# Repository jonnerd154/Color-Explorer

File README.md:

# Color-Explorer
A simple PCB to allow students to explore colors and mixing colors of light.

The board provides three slider potentiometers which each control the brightness of one color of light. There are four RGB LEDs. The first three show the individual color component as configured by the position of the sliders - one red, one blue, and one green. The fourth LED shows the mixed/combined colors. A jumper can be removed to disable the "mixed" LED, allowing students to set their sliders and make a hypothesis about what color will result from the mix. After recording their hypothesis, the jumper can be reinstalled to reveal the correct answer.

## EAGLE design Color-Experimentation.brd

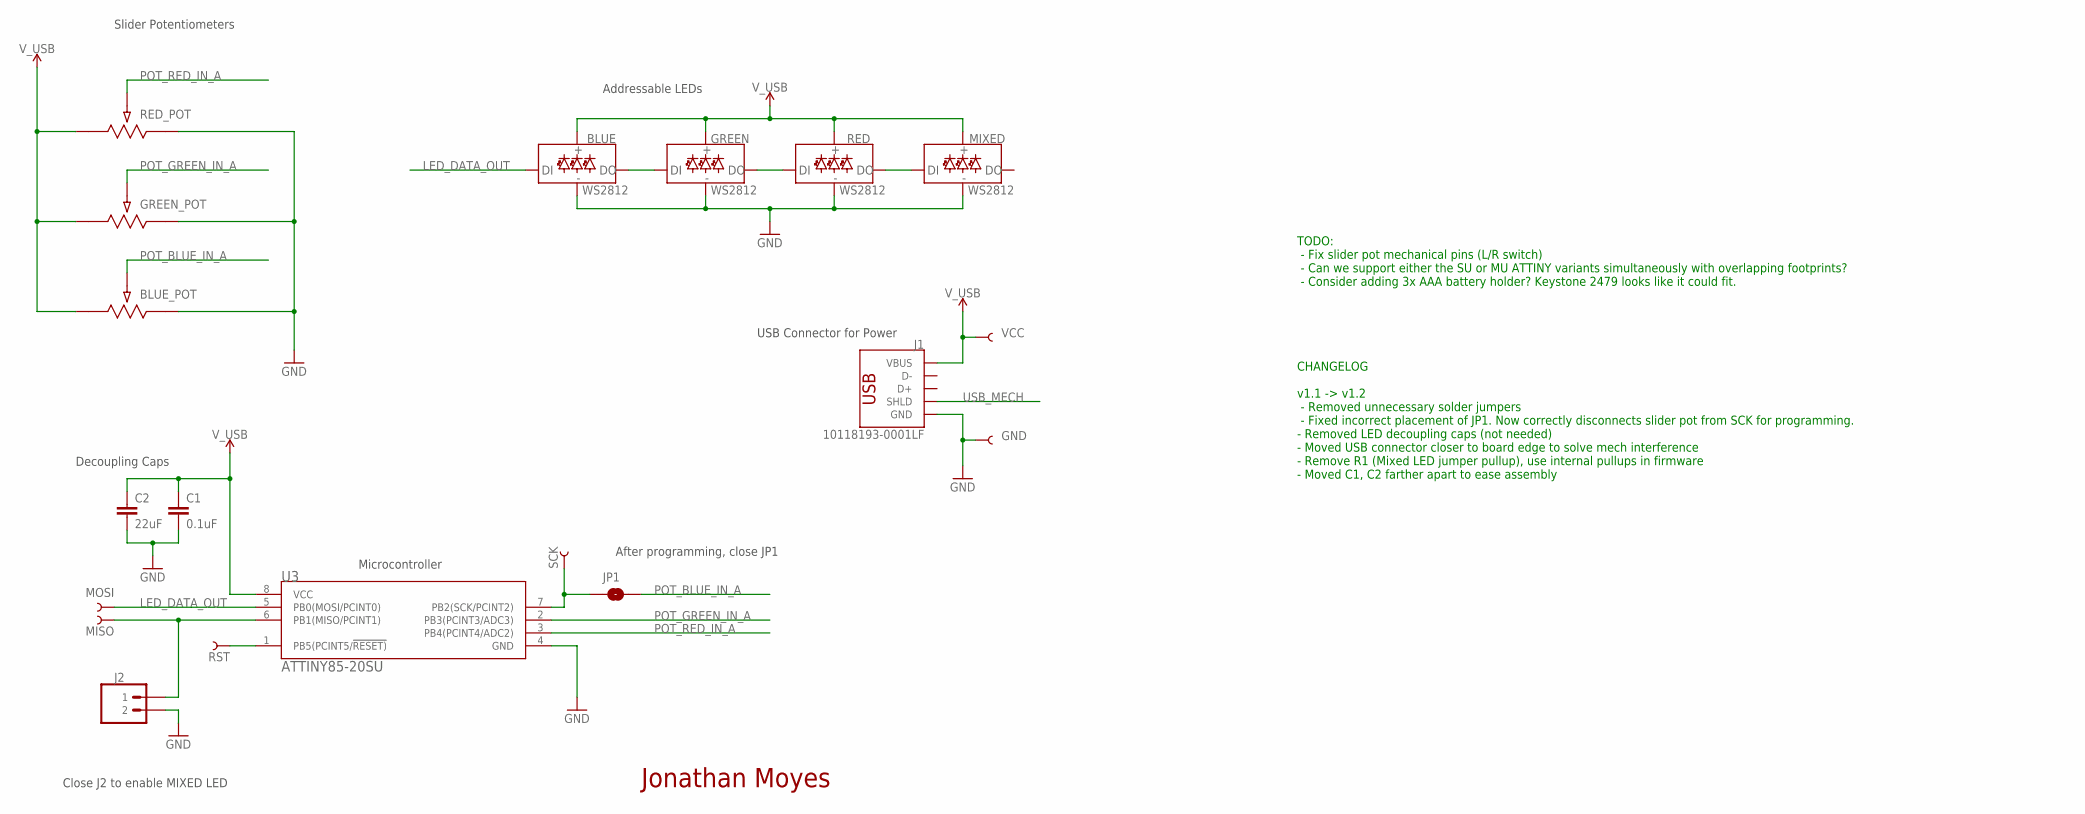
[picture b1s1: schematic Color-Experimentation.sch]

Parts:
BLUE: WS2812; WS2812-5X5-4PIN
BLUE_POT: 10k; POT_PTA2043
C1: 0.1uF; CAP_0603
C2: 22uF; C0603
GND: TEST-POINT40MIL; TESTPOINT_40MIL_ROUND
GREEN: WS2812; WS2812-5X5-4PIN
GREEN_POT: 10k; POT_PTA2043
J1: 10118193-0001LF; CONN_10118193-0001LF_AMP
J2: CONN_02; 1X02
JP1: JUMPER-SMT_2_NO_SILK; SMT-JUMPER_2_NO_SILK
MISO: TEST-POINT40MIL; TESTPOINT_40MIL_ROUND
MIXED: WS2812; WS2812-5X5-4PIN
MOSI: TEST-POINT40MIL; TESTPOINT_40MIL_ROUND
RED: WS2812; WS2812-5X5-4PIN
RED_POT: 10k; POT_PTA2043
RST: TEST-POINT40MIL; TESTPOINT_40MIL_ROUND
SCK: TEST-POINT40MIL; TESTPOINT_40MIL_ROUND
U3: ATTINY85-20SU; SOIC127P798X216-8N
VCC: TEST-POINT40MIL; TESTPOINT_40MIL_ROUND

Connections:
GND: BLUE.GND, BLUE_POT.3, C1.2, C2.2, GND.P$1, GREEN.GND, GREEN_POT.3, J1.5 (GND), J2.1 (2), MIXED.GND, RED.GND, RED_POT.3, U3.4 (GND)
LED_DATA_OUT: BLUE.DI, MOSI.P$1, U3.5 (PB0(MOSI/PCINT0))
unnamed: BLUE.DO, GREEN.DI
unnamed: GREEN.DO, RED.DI
unnamed: RST.P$1, U3.1 (PB5(PCINT5/!RESET))
unnamed: MIXED.DI, RED.DO
unnamed: J2.2 (1), MISO.P$1, U3.6 (PB1(MISO/PCINT1))
unnamed: JP1.1, SCK.P$1, U3.7 (PB2(SCK/PCINT2))
POT_BLUE_IN_A: BLUE_POT.WIPER (2), JP1.2
POT_GREEN_IN_A: GREEN_POT.WIPER (2), U3.2 (PB3(PCINT3/ADC3))
POT_RED_IN_A: RED_POT.WIPER (2), U3.3 (PB4(PCINT4/ADC2))
USB_MECH: J1.4 (SHLD), J1.6 (SHLD), J1.7 (SHLD), J1.8 (SHLD), J1.9 (SHLD), J1.S_1 (SHLD), J1.S_1_H1 (SHLD), J1.S_1_H2 (SHLD), J1.S_2 (SHLD), J1.S_2_H1 (SHLD), J1.S_2_H2 (SHLD)
V_USB: BLUE.VCC, BLUE_POT.1, C1.1, C2.1, GREEN.VCC, GREEN_POT.1, J1.1 (VBUS), MIXED.VCC, RED.VCC, RED_POT.1, U3.8 (VCC), VCC.P$1

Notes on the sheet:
Decoupling Caps
After programming, close JP1
USB Connector for Power
Addressable LEDs
Slider Potentiometers
Microcontroller
Close J2 to enable MIXED LED
Jonathan Moyes
CHANGELOG v1.1 -> v1.2 - Removed unnecessary solder jumpers - Fixed incorrect placement of JP1. Now correctly disconnects slider pot from SCK for programming. - Removed LED decoupling caps (not needed) - Moved USB connector closer to board edge to solve mech interference - Remove R1 (Mixed LED jump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
TODO: - Fix slider pot mechanical pins (L/R switch) - Can we support either the SU or MU ATTINY variants simultaneously with overlapping footprints? - Consider adding 3x AAA battery holder? Keystone 2479 looks like it could fit.

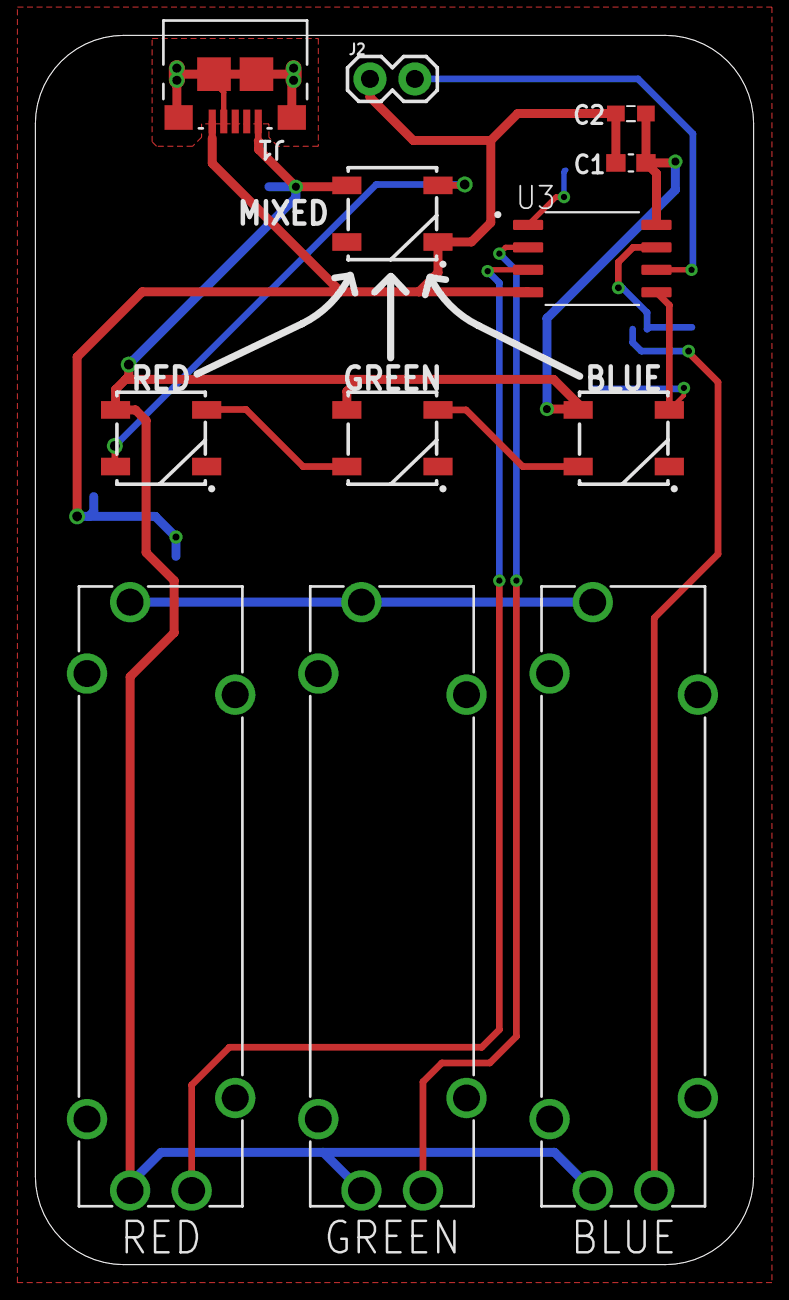
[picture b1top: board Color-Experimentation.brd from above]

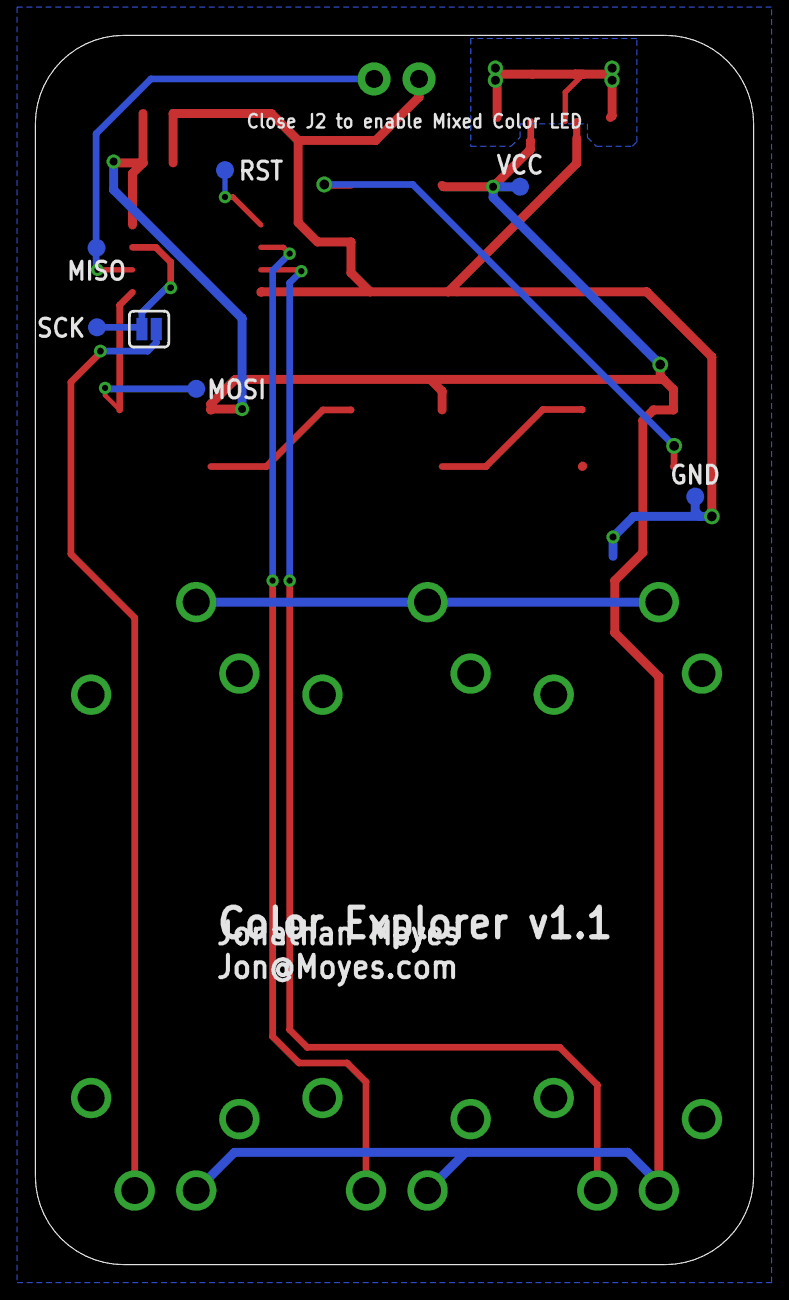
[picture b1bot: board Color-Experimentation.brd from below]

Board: 2 copper layers, 40.6 x 69.5 mm, 19 parts (7 on the bottom side), 13 nets.

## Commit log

2021-11-06 Cleanup schematic and routing
2021-11-06 Export component library
2021-11-06 Use LBR, cleanup, export Bill of Materials
2021-11-06 Add pullup, solder jumper on "mixed LED enable"
2021-11-06 Move corner of board to 0,0
2021-11-06 add attribution to sch
2021-11-06 Schematic to PDF
2021-11-06 ignore .DS_Store files
2021-11-06 add CAM file, include t/bNames in silkscreen
2021-11-06 Run CAM
2021-11-08 add 3d models, fusion push
2022-01-18 Add assembly images & stepfile
2022-01-18 move images
2022-11-17 Switch microcontroller for availability: v1.1
2022-11-26 Various improvements to address #2
2022-11-26 Initial commit: firmware
2022-11-26 Update PDF Schematic
